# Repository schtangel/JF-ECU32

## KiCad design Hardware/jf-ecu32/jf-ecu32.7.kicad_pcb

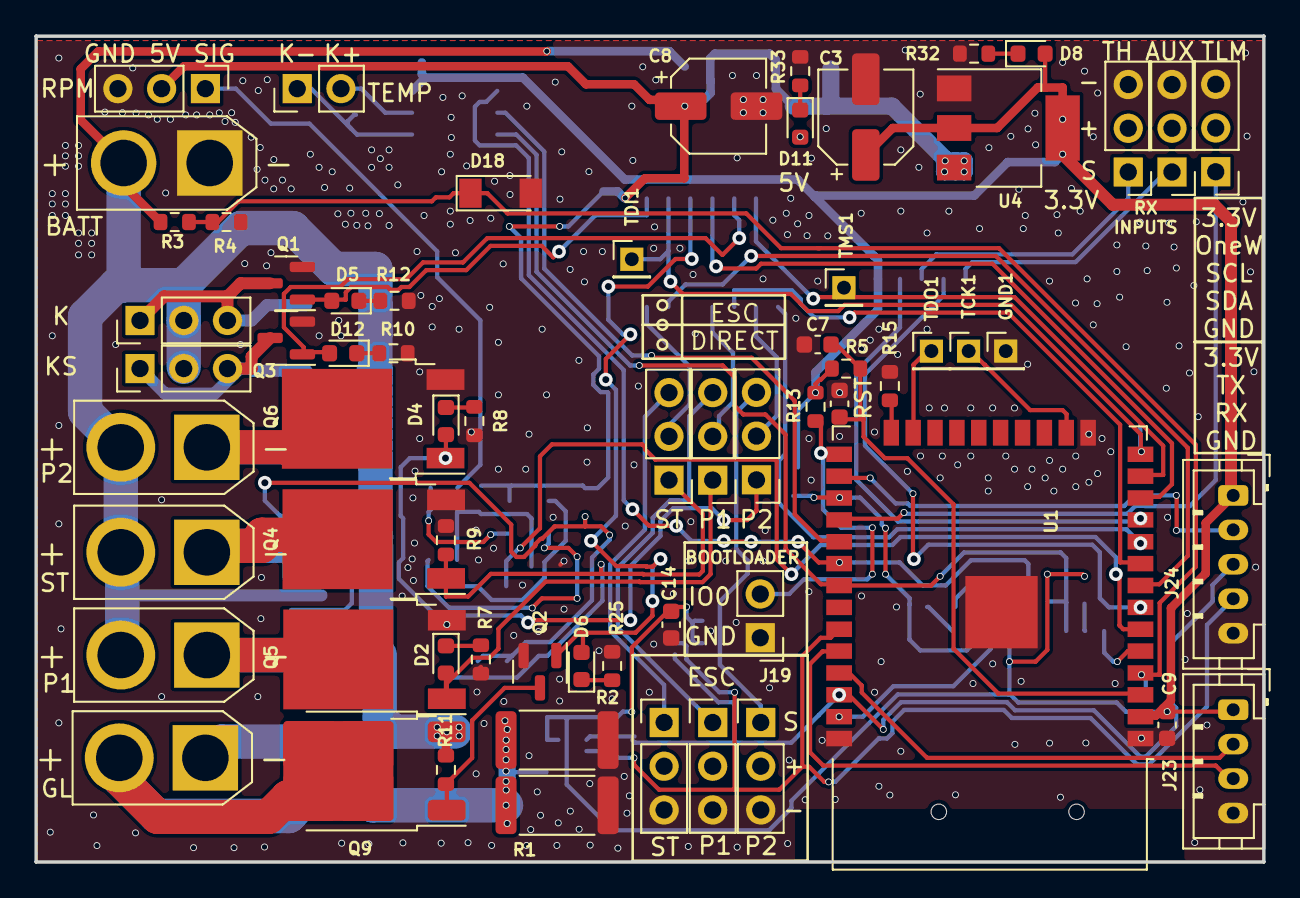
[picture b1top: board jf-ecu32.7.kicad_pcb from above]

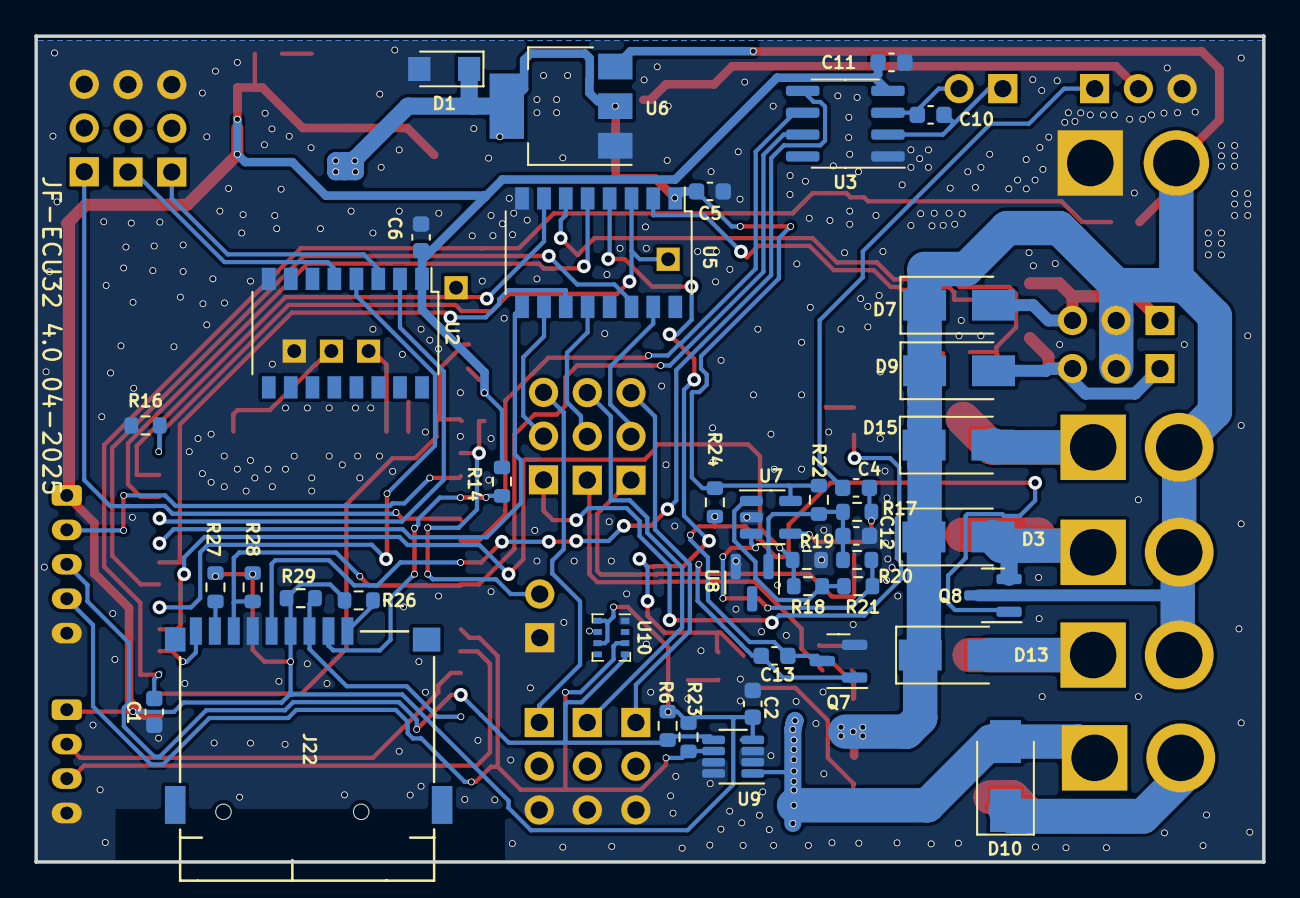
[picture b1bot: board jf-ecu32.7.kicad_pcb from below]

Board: 2 copper layers, 71.3 x 48.0 mm, 107 parts (42 on the bottom side), 70 nets.

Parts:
C1, C7, C13: 1µF; C_0603_1608Metric
C2, C4, C5, C6, C9, C10, C11, C12, C14: 0.1µF; C_0603_1608Metric
C3, C8: 22µF; CP_Elec_5x3
D1: SMF5V0A; D_SMF
D2, D4, D5, D6, D8, D11, D12: LED; LED_0603_1608Metric
D3, D10, D13, D15: D_Schottky SS34; D_SMA
D7, D9: D_Schottky SS14; D_SMA
D18: BZV55C3V3; D_MiniMELF
GND1: Conn_01x01_Male; PinHeader_1x01_P2.00mm_Vertical
J1: GAZ; PinHeader_1x03_P2.54mm_Vertical
J2: AUX; PinHeader_1x03_P2.54mm_Vertical
J3, J13, J16: PPM/PWM; PinHeader_1x03_P2.54mm_Vertical
J4: STARTER; PinHeader_1x03_P2.54mm_Vertical
J5: GLOW; AMASS_XT30U-F_1x02_P5.0mm_Vertical
J6: VANNE KEROSTART; PinHeader_1x03_P2.54mm_Vertical
J7: VANNE KERO; PinHeader_1x03_P2.54mm_Vertical
J8: BATTERY 2S/3S; AMASS_XT30U-M_1x02_P5.0mm_Vertical
J9: STARTER; AMASS_XT30U-F_1x02_P5.0mm_Vertical
J10: k; PinHeader_1x02_P2.54mm_Vertical
J11: RPM; PinHeader_1x03_P2.54mm_Vertical
J12: S.PORT; PinHeader_1x03_P2.54mm_Vertical
J14: PUMP1; AMASS_XT30U-F_1x02_P5.0mm_Vertical
J15: PUMP1; PinHeader_1x03_P2.54mm_Vertical
J17: PUMP2; AMASS_XT30U-F_1x02_P5.0mm_Vertical
J18: PUMP2; PinHeader_1x03_P2.54mm_Vertical
J19: EN; PinHeader_1x02_P2.54mm_Vertical
J22: Micro_SD_Card_Det1; J_SD_Card-micro_socket_A
J23: Conn_01x04; JST_PH_B4B-PH-K_1x04_P2.00mm_Vertical
J24: Conn_01x05; JST_PH_B5B-PH-K_1x05_P2.00mm_Vertical
Q1, Q2, Q3, Q7, Q8: A49T; SOT-23
Q4, Q5, Q6: LR8726; TO-252-2
Q9: FDD6685; TO-252-2
R1, R2: R020; R_2512_6332Metric
R3, R5, R7, R8, R9, R10, R11, R12, R13, R14, R15, R16, R25, R26, R27, R28, R29, R32, R33: 10K; R_0603_1608Metric
R4: 2.7K; R_0603_1608Metric
R6, R23: 1K; R_0603_1608Metric
R17, R18, R19, R20, R21: 20K; R_0603_1608Metric
R22: 500; R_0603_1608Metric
R24: 100K; R_0603_1608Metric
RST1: BOOT; C_0603_1608Metric
TCK1: Conn_01x01_Male; PinHeader_1x01_P2.00mm_Vertical
TDI1: Conn_01x01_Male; PinHeader_1x01_P2.00mm_Vertical
TDO1: Conn_01x01_Male; PinHeader_1x01_P2.00mm_Vertical
TMS1: Conn_01x01_Male; PinHeader_1x01_P2.00mm_Vertical
U1: ESP32-WROOM-32D; ESP32-WROOM-32
U2, U5: 4050; SOP-16_4.4x10.4mm_P1.27mm
U3: MAX31855KASA; SOIC-8_3.9x4.9mm_P1.27mm
U4: AMS1117-3.3; SOT-223-3_TabPin2
U6: AMS1117-5.0; SOT-223-3_TabPin2
U7: OPA340NA; SOT-23-5
U8: LM4040DBZ-2.5; SOT-23
U9: INA219AxDCN; SOT-23-8
U10: BMP280; Bosch_LGA-8_2x2.5mm_P0.65mm_ClockwisePinNumbering

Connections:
3.3V: C2.1, C3.1, C6.1, C9.1, C11.1, C14.1, D8.2 (A), J22.4 (VDD), J23.1, J24.1, R5.1, R6.2, R13.1, R14.2, R23.2, R26.2, R27.2, R28.2, R29.2, U1.2 (VDD), U2.1 (VCC), U3.4 (VCC), U4.2 (VO), U9.4 (VS), U10.6 (VDDIO), U10.8 (VDD)
+2V5: C12.1, R17.1, R20.1, R22.2, U8.1 (K)
+5V: C5.1, C8.1, D1.1 (A1), D11.2 (A), J11.2, R22.1, R24.1, U4.3 (VI), U5.1 (VCC), U6.2 (VO), U7.5 (V+)
+BATT: D3.1 (K), D7.1 (K), D9.1 (K), D13.1 (K), D15.1 (K), J6.2, J7.2, J8.2, J9.2, J14.2, J17.2, Q8.3 (D), Q9.3 (S), R3.1, R11.2, U6.3 (VI)
AUX: U1.7 (IO35), U2.4
AUX_5V: J2.1, U2.5
BR_MOSFET: C13.1, Q7.3 (D), Q8.1 (G), R24.2
CLK: J22.5 (CLK), U1.30 (IO18), U3.5 (SCK)
CS_MAX31855: U1.29 (IO5), U3.6 (~CS)
ESP_SCL: J24.3, R6.1, U1.36 (IO22), U9.5 (SCL), U10.4 (SCK)
ESP_SDA: J24.4, R23.1, U1.33 (IO21), U9.6 (SDA), U10.3 (SDI)
GND: C1.2, C2.2, C3.2, C5.2, C6.2, C7.2, C8.2, C9.2, C11.2, C12.2, C14.2, D1.2 (A2), D18.2 (A), GND1.1, J1.3, J2.3, J4.3, J8.1, J11.3, J12.3, J15.3, J18.3, J19.1, J22.6 (VSS), J23.4, J24.5, Q1.2 (S), Q2.2 (S), Q3.2 (S), Q4.3 (S), Q5.3 (S), Q6.3 (S), Q7.2 (S), R1.2, R2.2, R4.2, R7.2, R8.2, R9.2, R10.2, R12.1, R15.2, R16.1, R19.1, R25.2, R32.2, R33.2, RST1.2, U1.1 (GND), U1.15 (GND), U1.38 (GND), U1.39 (GND), U2.8 (VSS), U3.1 (GND), U4.1 (GND), U5.8 (VSS), U6.1 (GND), U7.2 (V-), U8.2 (A), U9.2 (IN-), U9.3 (GND), U9.7 (A0), U9.8 (A1), U10.1 (GND), U10.7 (GND)
IO0: J19.2, R13.2, U1.25 (IO0)
MISO: J22.7 (DAT0), R28.1, U1.31 (IO19), U3.7 (SO)
MOSI: J22.3 (CMD), R29.1, U1.37 (IO23)
unnamed: D2.1 (K), R7.1
unnamed: D3.2 (A), J9.1, Q4.2 (D), Q8.2 (S)
unnamed: D4.1 (K), R8.1
unnamed: D5.1 (K), R12.2
unnamed: D6.1 (K), R25.1
unnamed: D7.2 (A), J7.1, J7.3, Q1.3 (D)
unnamed: D8.1 (K), R32.1
unnamed: D9.2 (A), J6.1, J6.3, Q3.3 (D)
unnamed: D10.2 (A), J5.1, R1.1, R2.1, U9.1 (IN+)
unnamed: D10.1 (K), J5.2, Q9.2 (D)
unnamed: D11.1 (K), R33.1
unnamed: D12.1 (K), R10.1
unnamed: D13.2 (A), J14.1, Q5.2 (D)
unnamed: D15.2 (A), J17.1, Q6.2 (D)
unnamed: C10.2, J10.1, U3.2 (T-)
unnamed: C10.1, J10.2, U3.3 (T+)
unnamed: J22.8 (DAT1), R27.1
unnamed: J22.1 (DAT2), R26.1
unnamed: Q2.3 (D), Q9.1 (G), R11.1
unnamed: R18.2, R21.2, U7.1
unnamed: C7.1, R5.2, RST1.1, U1.3 (EN)
unnamed: R15.1, U1.24 (IO2)
unnamed: R20.2, R21.1, U7.3 (+)
unnamed: C4.2, R17.2, U7.4 (-)
OneWire: J24.2, U1.26 (IO4)
P1_MOSFET: D2.2 (A), J13.1, Q5.1 (G)
P1_OUTPUT: J13.3, J15.1
P2_MOSFET: D4.2 (A), J16.1, Q6.1 (G)
P2_OUTPUT: J16.3, J18.1
PPM_GAZ: U1.11 (IO26), U2.2
PPM_GAZ_5V: J1.1, U2.3
PPM_PWM_PUMP1: J13.2, U5.12
PPM_PWM_PUMP1_3.3: U1.9 (IO33), U5.11
PPM_PWM_PUMP2: J16.2, U5.10
PPM_PWM_PUMP2_3.3: U1.10 (IO25), U5.9
PPM_PWM_STARTER: J3.2, U5.15
PPM_STARTER_3.3: U1.8 (IO32), U5.14
PWM_GLOW: D6.2 (A), Q2.1 (G), U5.4
PWM_GLOW_3.3: U1.12 (IO27), U5.5
PWM_KERO: D5.2 (A), Q1.1 (G), U5.2
PWM_KEROSTART: D12.2 (A), Q3.1 (G), U5.6
PWM_KEROSTART_3.3: TMS1.1, U1.13 (IO14), U5.7
PWM_KERO_3.3: R16.2, TDI1.1, U1.14 (IO12), U5.3
RPM: C4.1, J11.1
RPM-2: R18.1, R19.2, U1.6 (IO34)
RX: J23.3, U1.34 (RXD0/IO3)
SD_CS: J22.2 (DAT3/CD), R14.1, U1.27 (IO16)
SD_DET: J22.9 (DET), U1.5 (SENSOR_VN)
ST_MOSFET: C13.2, J3.1, Q4.1 (G), Q7.1 (G), R9.1
ST_OUTPUT: J3.3, J4.1
TCK: TCK1.1, U1.16 (IO13)
TDO: TDO1.1, U1.23 (IO15)
TX: J23.2, U1.35 (TXD0/IO1)
TX2: J12.1, U1.28 (IO17)
VBAT_ADC: C1.1, D18.1 (K), R3.2, R4.1, U1.4 (SENSOR_VP)

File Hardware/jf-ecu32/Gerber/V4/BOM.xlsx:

Designators | Qty | Footprint | Partname | LCSC Part # | Mfr. Part # | Manufacturer | LCSC Link
C1, C13, C7, RST1 | 4 | 0603 | 1µF | C6266891 | TCC0603X5R105M250CT | s | https://www.lcsc.com/product-detail/C6266891.html
C10, C11, C12, C14, C2, C4, C5, C6, C9 | 9 | 0603 | 0.1µF | C1590 | CL10B104KA8NNNC | s | https://www.lcsc.com/product-detail/C1590.html
C3, C8 | 2 | CP_Elec_5x3 | 22µF | C23289 | RVT1V220M0505 | s | https://www.lcsc.com/product-detail/C23289.html
D1 | 1 | D_SMF | SMF5V0A | C1972946 | SMF5V0A-E3-08 | s | https://www.lcsc.com/product-detail/C1972946.html
D10, D13, D15, D3 | 4 | D_SMA | D_Schottky SS34 | C83961 | SS34 | s | https://www.lcsc.com/product-detail/C83961.html
D11, D12, D2, D4, D5, D6, D8 | 7 | 0603 | LED | C2290 | KT-0603W | s | https://www.lcsc.com/product-detail/C2290.html
D18 | 1 | D_MiniMELF | BZV55C3V3 | C545323 | BZV55C3V3 | s | https://www.lcsc.com/product-detail/C545323.html
D7, D9 | 2 | D_SMA | D_Schottky SS14 | C2480 | SS14 | s | https://www.lcsc.com/product-detail/C2480.html
J22 | 1 | J_SD_Card-micro_socket_A | TF-01A | C91145 | TF-01A | s | https://www.lcsc.com/product-detail/C91145.html
Q1, Q2, Q3, Q7, Q8 | 5 | SOT-23 | A49T | C30010 | AO3404A | s | https://www.lcsc.com/product-detail/C30010.html
Q4, Q5, Q6 | 3 | TO-252-2 | LR8726 | C81137 | IRLR8726TRPBF | s | https://www.lcsc.com/product-detail/C81137.html
Q9 | 1 | TO-252-2 | FDD6685 | C10866 | FDD6685 | s | https://www.lcsc.com/product-detail/C10866.html
R1, R2 | 2 | 2512 | 20 | C6966148 | RC2512JK-7W20RL | s | https://www.lcsc.com/product-detail/C6966148.html
R10, R11, R12, R13, R14, R15, R16, R25, R26, R27, R28, R29, R3, R32, R33, R5, R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 | 19 | 0603 | 10K | C25804 | 0603WAF1002T5E | s | https://www.lcsc.com/product-detail/C25804.html
R17, R18, R19, R20, R21 | 5 | 0603 | 20K | C4184 | 0603WAF2002T5E | s | https://www.lcsc.com/product-detail/C4184.html
R22 | 1 | 0603 | 500 | C6207671 | RT0603BRD07500RL | s | https://www.lcsc.com/product-detail/C6207671.html
R23, R6 | 2 | 0603 | 1K | C21190 | 0603WAF1001T5E | s | https://www.lcsc.com/product-detail/C21190.html
R24 | 1 | 0603 | 100K | C25803 | 0603WAF1003T5E | s | https://www.lcsc.com/product-detail/C25803.html
R4 | 1 | 0603 | 2.7K | C13167 | 0603WAF2701T5E | s | https://www.lcsc.com/product-detail/C13167.html
U1 | 1 | ESP32-WROOM-32 | ESP32-WROOM-32D-N16 | C529578 | ESP32-WROOM-32D-N16 | s | https://www.lcsc.com/product-detail/C529578.html
U10 | 1 | Bosch_LGA-8_2x2.5mm_P0.65mm_ClockwisePinNumbering | BMP280 | C83291 | BMP280 | s | https://www.lcsc.com/product-detail/C83291.html
U2, U5 | 2 | SOP-16_4.4x10.4mm_P1.27mm | cd4050bms | C507165 | CD4050BM/TR | s | https://www.lcsc.com/product-detail/C507165.html
U3 | 1 | SOIC-8_3.9x4.9mm_P1.27mm | MAX31855KASA | C52028 | MAX31855KASA+T | s | https://www.lcsc.com/product-detail/C52028.html
U4 | 1 | SOT-223-3_TabPin2 | AMS1117-3.3 | C6186 | AMS1117-3.3 | s | https://www.lcsc.com/product-detail/C6186.html
U6 | 1 | SOT-223-3_TabPin2 | AMS1117-5.0 | C6187 | AMS1117-5.0 | s | https://www.lcsc.com/product-detail/C6187.html
U7 | 1 | SOT-23-5 | OPA340NA | C49056105 | XOPA340NA | s | https://www.lcsc.com/product-detail/C49056105.html
U8 | 1 | SOT-23 | LM4040DBZ-2.5 | C2156826 | LM4040CIM3-2.5+T | s | https://www.lcsc.com/product-detail/C2156826.html
U9 | 1 | SOT-23-8 | INA219AxDCN | C87469 | INA219AIDCNR | s | https://www.lcsc.com/product-detail/C87469.html

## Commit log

2026-02-22 Add manufacturing files for v4 version
